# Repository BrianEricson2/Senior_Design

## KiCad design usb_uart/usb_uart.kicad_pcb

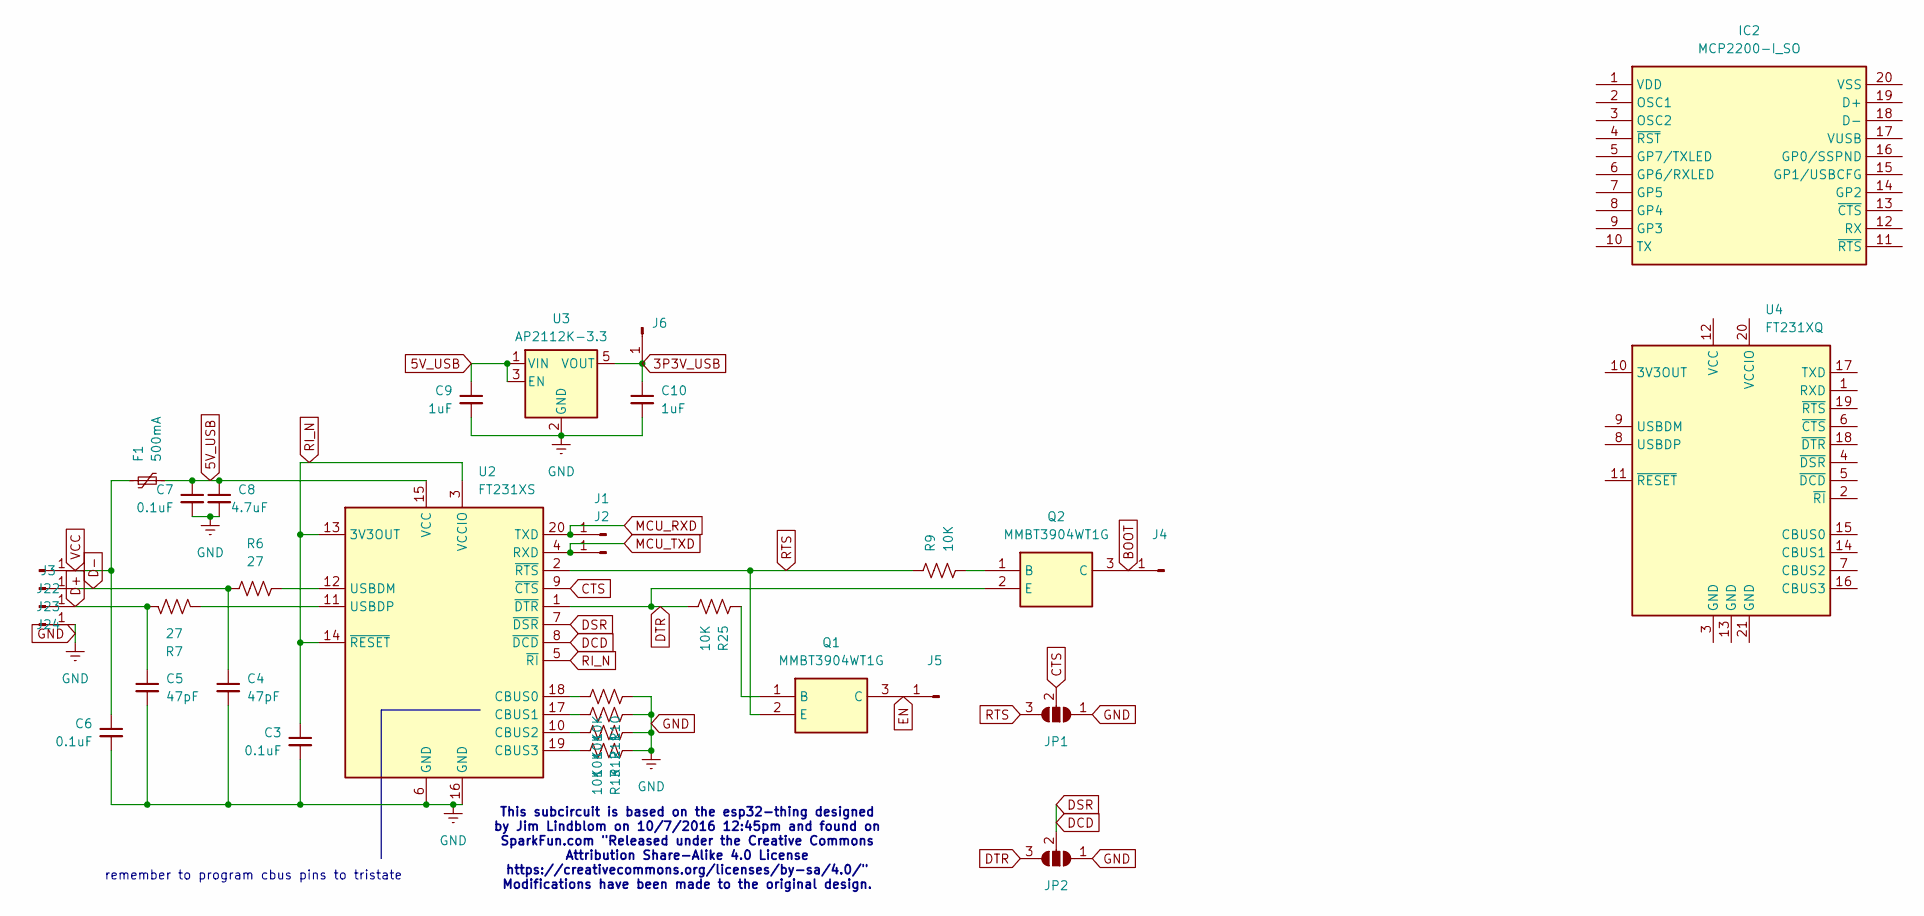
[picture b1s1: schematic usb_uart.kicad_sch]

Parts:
C3, C6, C7: 0.1uF; C_1206_3216Metric_Pad1.33x1.80mm_HandSolder
C4, C5: 47pF; C_1206_3216Metric_Pad1.33x1.80mm_HandSolder
C8: 4.7uF; C_1206_3216Metric_Pad1.33x1.80mm_HandSolder
C9, C10: 1uF; C_1206_3216Metric_Pad1.33x1.80mm_HandSolder
F1: 500mA; Fuse_1206_3216Metric_Pad1.42x1.75mm_HandSolder
IC2: MCP2200-I_SO; SOIC127P1030X265-20N; Mouser Part Number 579-MCP2200-I/SO
J1, J2, J3, J4, J5, J6, J22, J23, J24: Conn_01x01_Pin; PinHeader_1x01_P2.00mm_Vertical
JP1, JP2: SolderJumper_3_Open; SolderJumper-3_P1.3mm_Open_RoundedPad1.0x1.5mm_NumberLabels
Q1, Q2: MMBT3904WT1G; SOT65P220X100-3N; Mouser Part Number 863-MMBT3904WT1G
R6, R7: 27; R_1206_3216Metric_Pad1.30x1.75mm_HandSolder
R9, R10, R11, R12, R13, R25: 10K; R_1206_3216Metric_Pad1.30x1.75mm_HandSolder
U2: FT231XS; SSOP-20_3.9x8.7mm_P0.635mm
U3: AP2112K-3.3; SOT-23-5
U4: FT231XQ; QFN-20-1EP_4x4mm_P0.5mm_EP2.5x2.5mm

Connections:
3P3V_USB: C10.1, J6.1, U3.5 (VOUT)
5V_USB: C7.1, C8.1, C9.1, F1.2, U2.15 (VCC), U3.1 (VIN), U3.3 (EN)
BOOT: J4.1, Q2.3 (C)
CTS: JP1.2 (C), U2.9 (~CTS)
D+: C5.1, J23.1, R7.2
D-: C4.1, J22.1, R6.2
DCD: JP2.2 (C), U2.7 (~DSR), U2.8 (~DCD)
DTR: JP2.3 (B), Q2.2 (E), R25.2, U2.1 (~DTR)
EN: J5.1, Q1.3 (C)
GND: C3.2, C4.2, C5.2, C6.2, C7.2, C8.2, C9.2, C10.2, J24.1, JP1.1 (A), JP2.1 (A), R10.1, R11.1, R12.1, R13.1, U2.6 (GND), U2.16 (GND), U3.2 (GND)
MCU_RXD: J1.1, U2.20 (TXD)
MCU_TXD: J2.1, U2.4 (RXD)
unnamed: Q1.1 (B), R25.1
unnamed: Q2.1 (B), R9.2
unnamed: R10.2, U2.18 (CBUS0)
unnamed: R11.2, U2.17 (CBUS1)
unnamed: R12.2, U2.10 (CBUS2)
unnamed: R13.2, U2.19 (CBUS3)
unnamed: R6.1, U2.12 (USBDM)
unnamed: R7.1, U2.11 (USBDP)
RI_N: C3.1, U2.3 (VCCIO), U2.5 (~RI), U2.13 (3V3OUT), U2.14 (~RESET)
RTS: JP1.3 (B), Q1.2 (E), R9.1, U2.2 (~RTS)
VCC: C6.1, F1.1, J3.1

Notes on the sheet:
This subcircuit is based on the esp32-thing designed by Jim Lindblom on 10/7/2016 12:45pm and found on SparkFun.com "Released under the Creative Commons Attribution Share-Alike 4.0 License https://creativecommons.org/licenses/by-sa/4.0/" Modifications have been made to the original design.
remember to program cbus pins to tristate

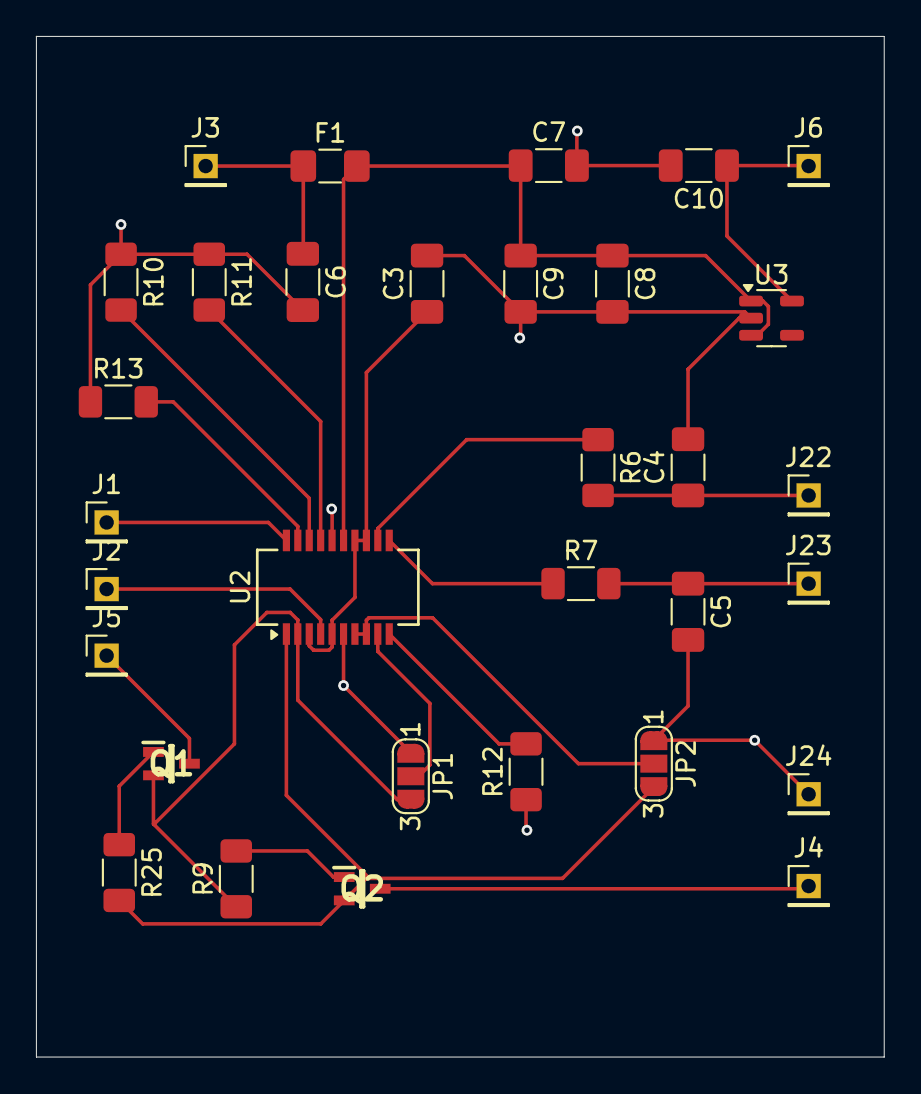
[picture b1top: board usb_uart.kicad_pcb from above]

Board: 2 copper layers, 47.1 x 56.7 mm, 32 parts (0 on the bottom side), 23 nets.

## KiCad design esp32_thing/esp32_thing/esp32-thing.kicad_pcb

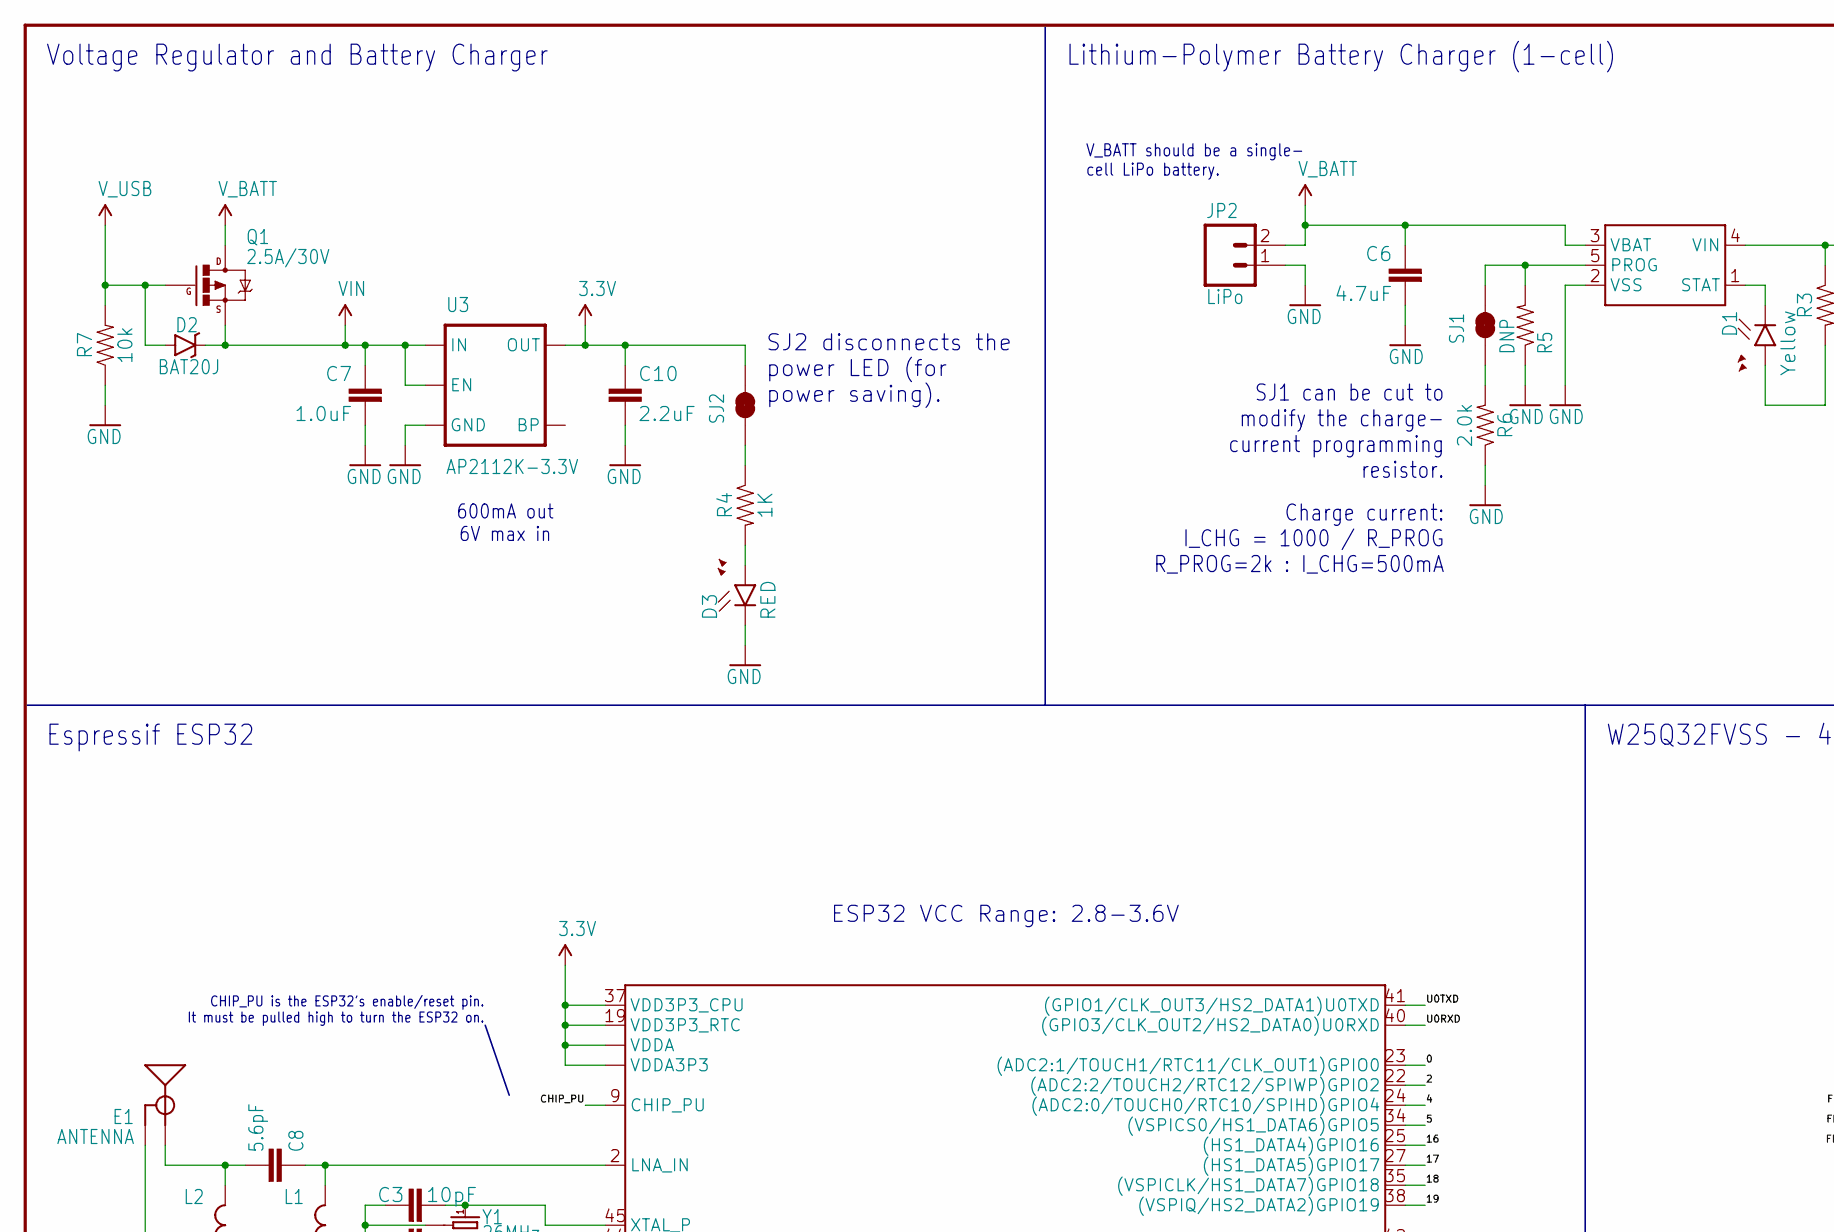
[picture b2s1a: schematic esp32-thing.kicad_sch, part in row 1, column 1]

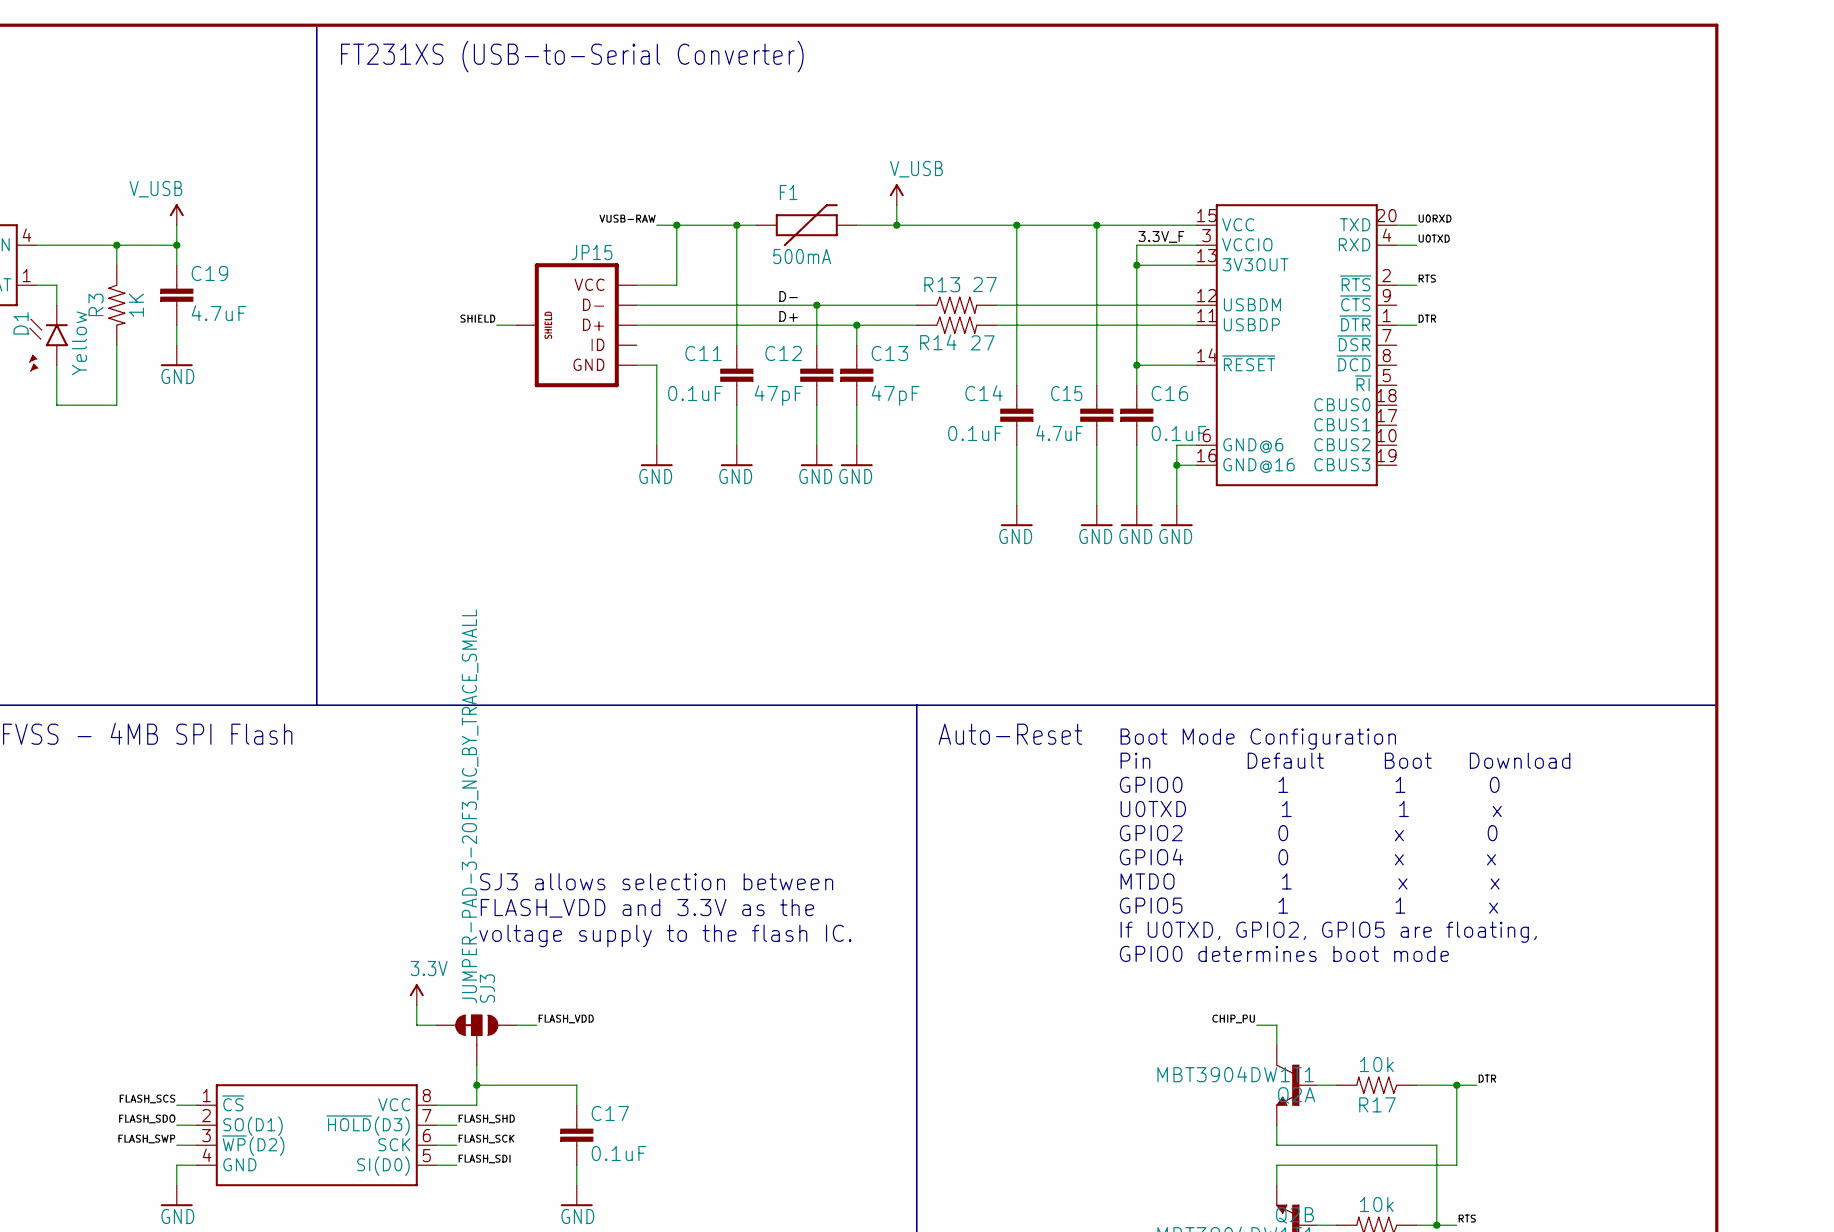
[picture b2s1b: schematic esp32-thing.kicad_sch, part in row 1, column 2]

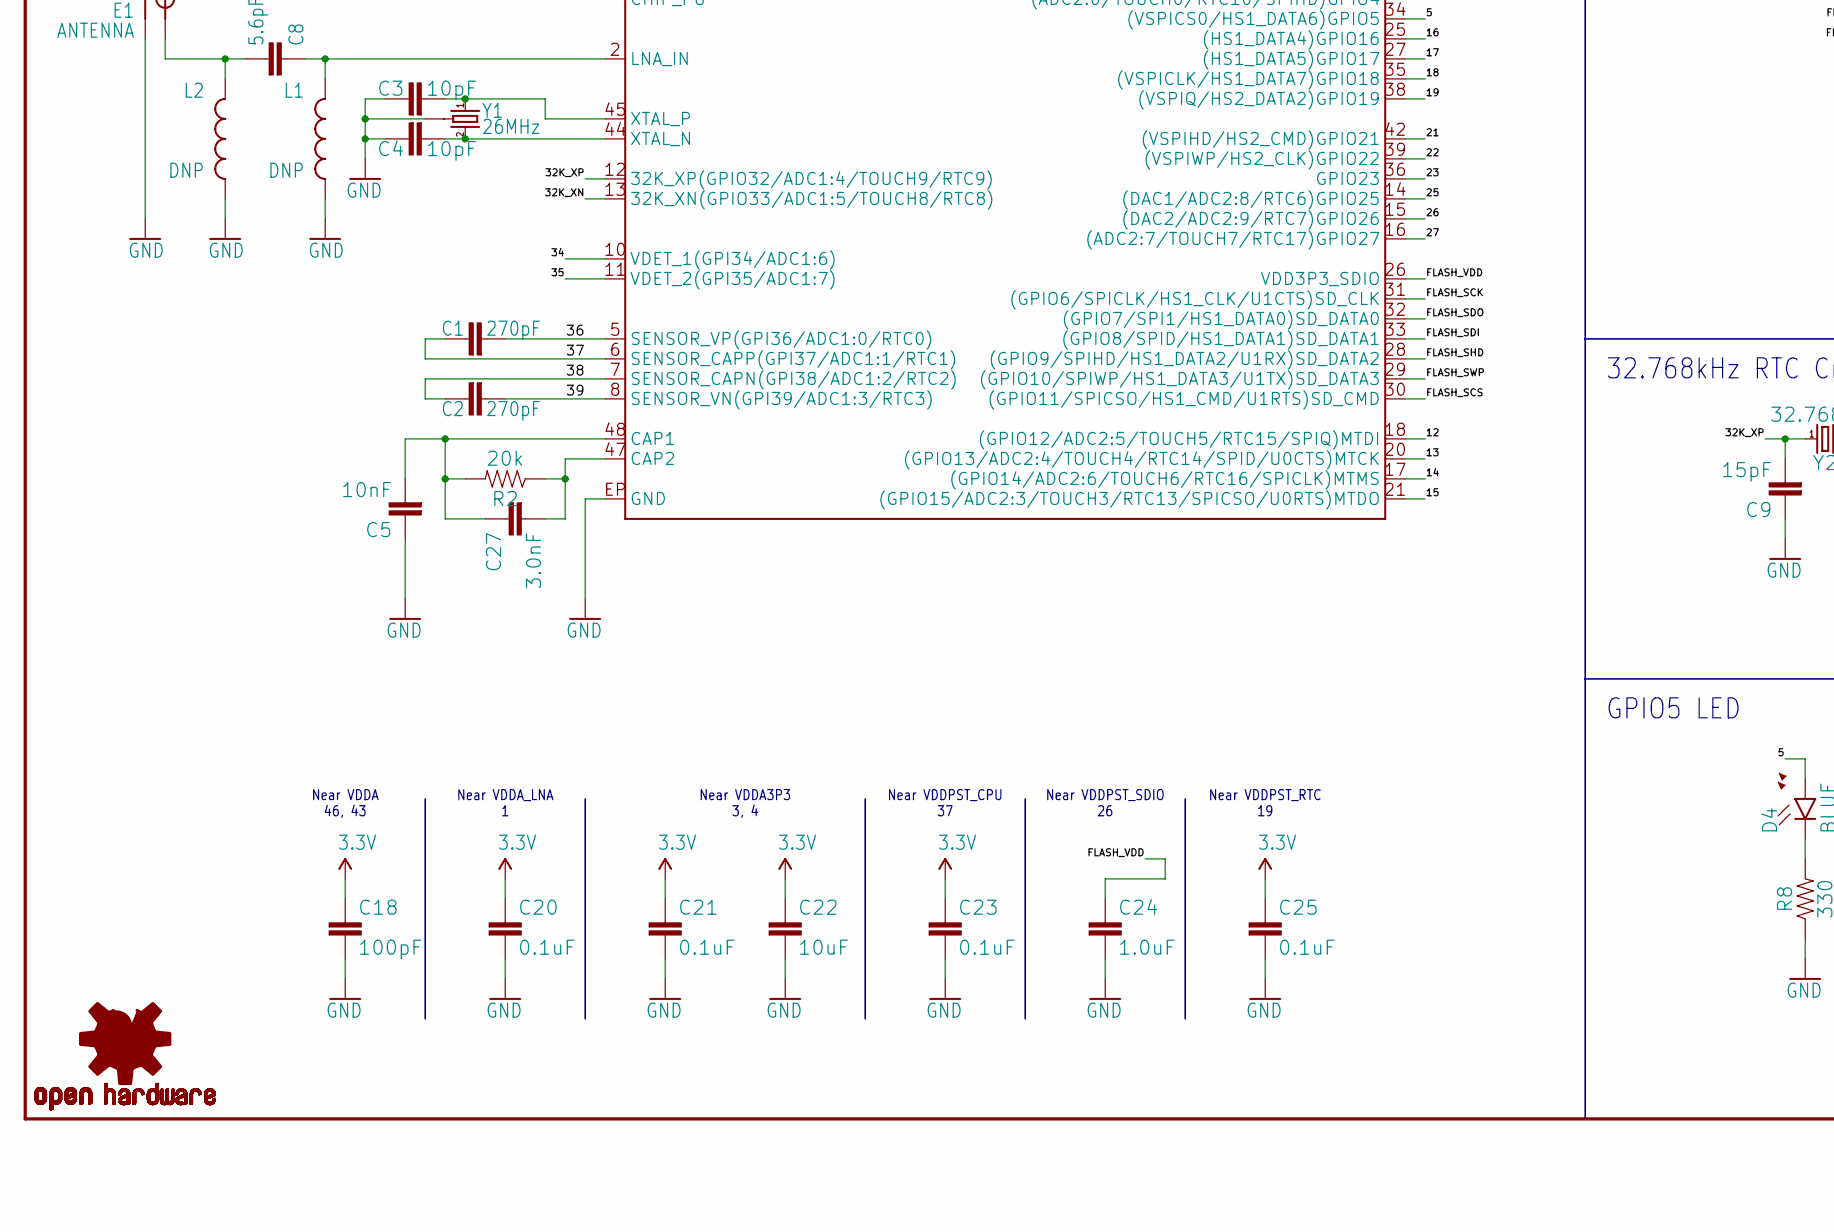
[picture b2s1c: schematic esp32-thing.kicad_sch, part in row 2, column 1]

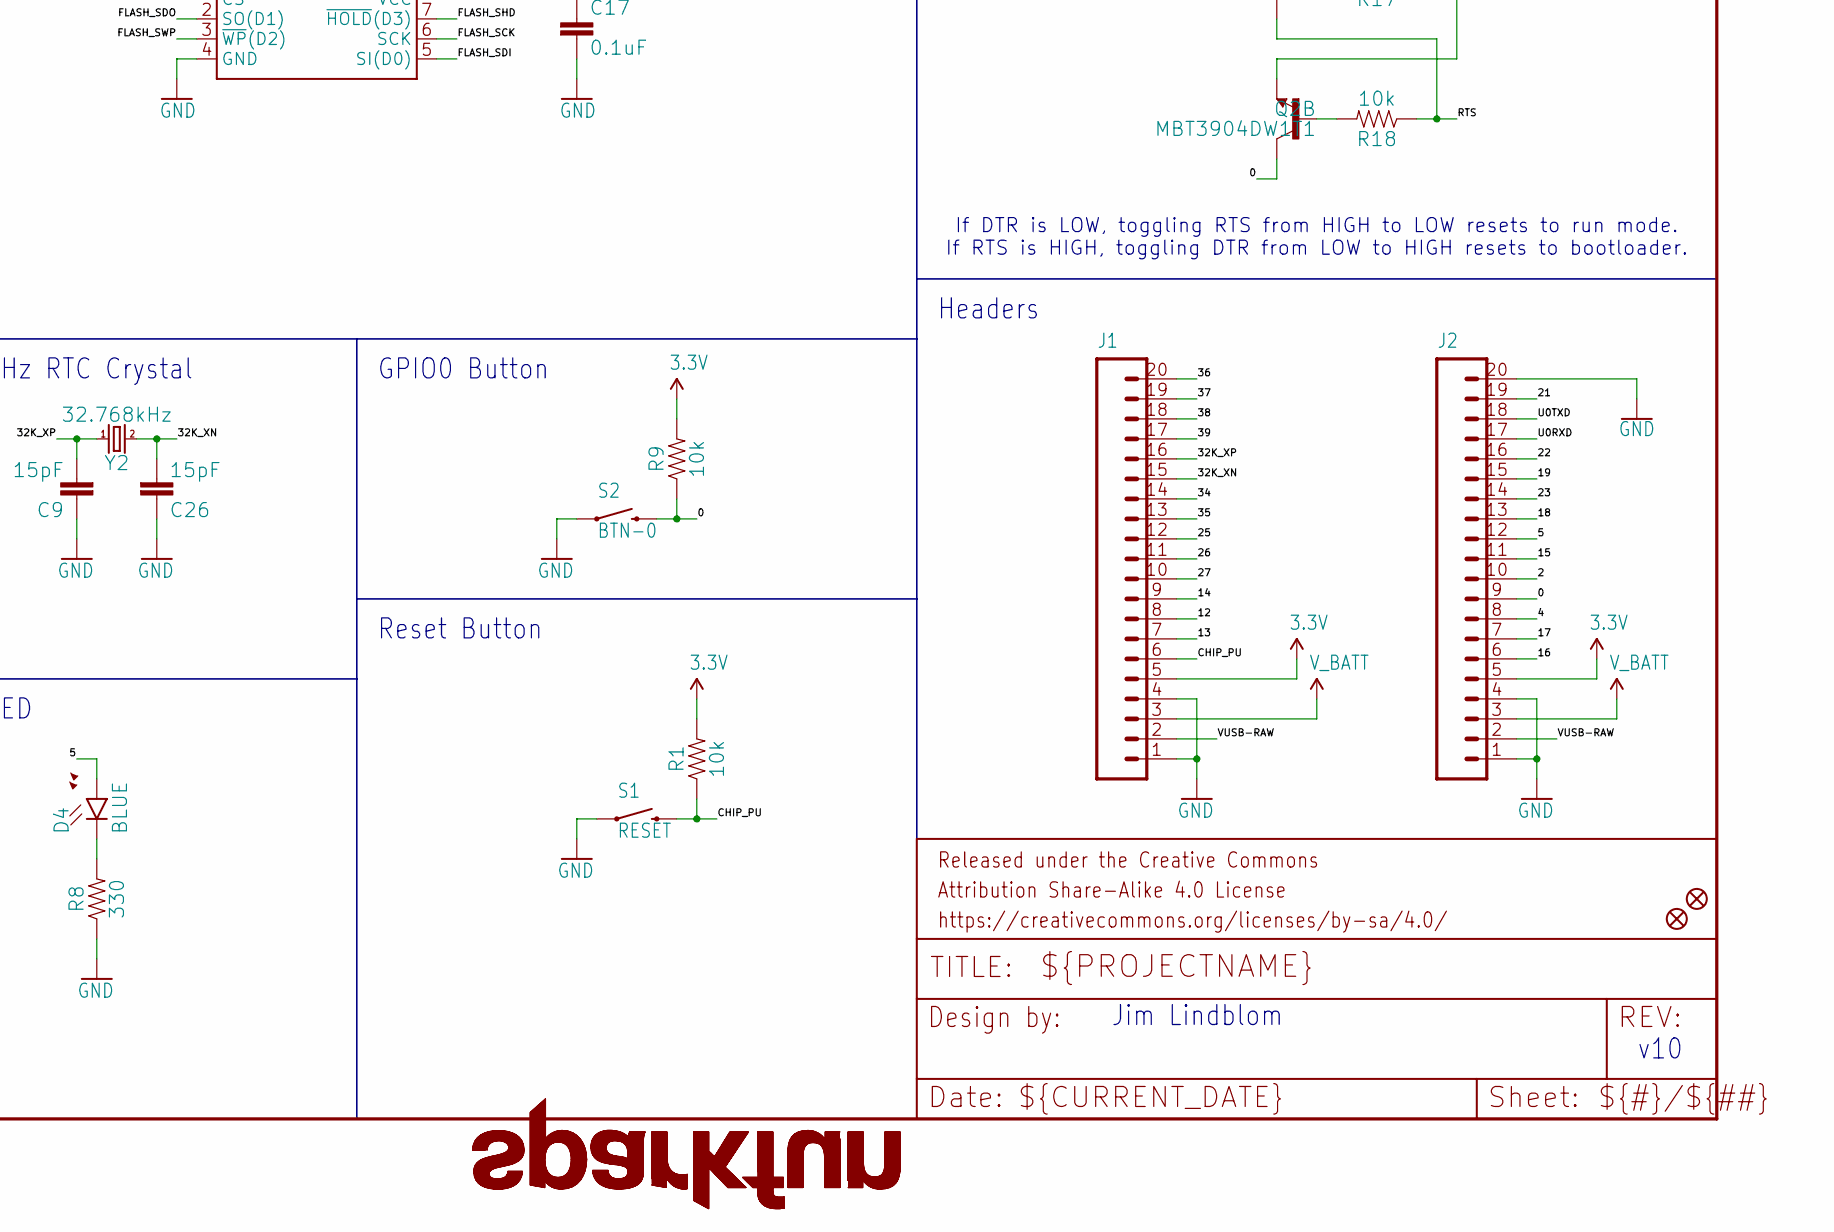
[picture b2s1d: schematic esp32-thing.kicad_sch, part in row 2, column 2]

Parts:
C1, C2: 270pF; 0603
C3, C4: 10pF; 0603
C5: 10nF; 0603
C6, C19: 4.7uF; 0603
C7: 1.0uF; 0805
C8: 5.6pF; 0603
C9, C26: 15pF; 0603
C10: 2.2uF; 0603
C11, C14, C16, C17, C20, C21, C23, C25: 0.1uF; 0603
C12, C13: 47pF; 0603
C15: 4.7uF; 0603-CAP
C18: 100pF; 0603
C22: 10uF; 0603
C24: 1.0uF; 0603
C27: 3.0nF; 0603
D1: Yellow; LED-0603
D2: BAT20J; SOD-323
D3: RED; LED-0603
D4: BLUE; LED-0603
E1: ANTENNA; TRACE_ANTENNA_2.4GHZ_25.7MM_TUNED
F1: 500mA; PTC-1206
FD1, FD2: FIDUCIALUFIDUCIAL; MICRO-FIDUCIAL
FRAME1: FRAME-LEDGER; CREATIVE_COMMONS
J1, J2: M20NOSILK; 1X20_NOSILK
JP2: LiPo; JST-2-PTH
JP15: USB_MICROB_PLUGCONN-11752; USB-B-MICRO-SMD_V03
L1, L2: DNP; 0603
LOGO1, LOGO3: SFE_LOGO_NAME.2_INCH; SFE_LOGO_NAME_.2
LOGO2: OSHW-LOGOMINI; OSHW-LOGO-MINI
Q1: 2.5A/30V; SOT23-3
Q2: MBT3904DW1T1; SC70-6
R1, R7, R9, R17, R18: 10k; 0603
R2: 20k; 0603
R3, R4: 1K; 0603
R5: DNP; 1_6W-RES
R6: 2.0k; 0603
R8: 330; 0603
R13, R14: 27; 0603
S1: RESET; TACTILE_SWITCH_SMD_4.6X2.8MM
S2: BTN-0; TACTILE_SWITCH_SMD_4.6X2.8MM
SJ1, SJ2: JUMPER-PAD-2-NC_BY_TRACE; PAD-JUMPER-2-NC_BY_TRACE_YES_SILK
SJ3: JUMPER-PAD-3-2OF3_NC_BY_TRACE_SMALL; PAD-JUMPER-3-2OF3_NC_BY_TRACE_YES_SILK_FULL_BOX
U1: MCP73831; SOT23-5
U2: ESP3212; QFN48-0.4MM
U3: AP2112K-3.3V; SOT23-5
U4: FT231XS; SSOP20_L
U5: W25Q32FVSS; SOIC-8
Y1: 26MHz; CRYSTAL-SMD-3.2X2.5
Y2: 32.768kHz; CRYSTAL-SMD-3.2X1.5MM

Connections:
0: J2.9, Q2.6 (C), R9.1, S2.3 (2), S2.4 (2), U2.23 ((ADC2:1/TOUCH1/RTC11/CLK_OUT1)GPIO0)
2: J2.10, U2.22 ((ADC2:2/TOUCH2/RTC12/SPIWP)GPIO2)
3.3V: C10.1, C18.1, C20.1, C21.1, C22.1, C23.1, C25.1, J1.5, J2.5, R1.2, R9.2, SJ2.2, SJ3.3, U2.1 (VDDA), U2.3 (VDDA3P3), U2.4 (VDDA3P3), U2.19 (VDD3P3_RTC), U2.37 (VDD3P3_CPU), U2.43 (VDDA), U2.46 (VDDA), U3.5 (OUT)
3.3V_F: C16.1, U4.3 (VCCIO), U4.13 (3V3OUT), U4.14 (~RESET)
4: J2.8, U2.24 ((ADC2:0/TOUCH0/RTC10/SPIHD)GPIO4)
5: D4.A, J2.12, U2.34 ((VSPICS0/HS1_DATA6)GPIO5)
12: J1.8, U2.18 ((GPIO12/ADC2:5/TOUCH5/RTC15/SPIQ)MTDI)
13: J1.7, U2.20 ((GPIO13/ADC2:4/TOUCH4/RTC14/SPID/U0CTS)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)
14: J1.9, U2.17 ((GPIO14/ADC2:6/TOUCH6/RTC16/SPICLK)MTMS)
15: J2.11, U2.21 ((GPIO15/ADC2:3/TOUCH3/RTC13/SPICSO/U0RT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)
16: J2.6, U2.25 ((HS1_DATA4)GPIO16)
17: J2.7, U2.27 ((HS1_DATA5)GPIO17)
18: J2.13, U2.35 ((VSPICLK/HS1_DATA7)GPIO18)
19: J2.15, U2.38 ((VSPIQ/HS2_DATA2)GPIO19)
21: J2.19, U2.42 ((VSPIHD/HS2_CMD)GPIO21)
22: J2.16, U2.39 ((VSPIWP/HS2_CLK)GPIO22)
23: J2.14, U2.36 (GPIO23)
25: J1.12, U2.14 ((DAC1/ADC2:8/RTC6)GPIO25)
26: J1.11, U2.15 ((DAC2/ADC2:9/RTC7)GPIO26)
27: J1.10, U2.16 ((ADC2:7/TOUCH7/RTC17)GPIO27)
32K_XN: C26.2, J1.15, U2.13 (32K_XN(GPIO33/ADC1:5/TOUCH8/RTC8)), Y2.P$2 (2)
32K_XP: C9.2, J1.16, U2.12 (32K_XP(GPIO32/ADC1:4/TOUCH9/RTC9)), Y2.P$1 (1)
34: J1.14, U2.10 (VDET_1(GPI34/ADC1:6))
35: J1.13, U2.11 (VDET_2(GPI35/ADC1:7))
36: C1.2, J1.20, U2.5 (SENSOR_VP(GPI36/ADC1:0/RTC0))
37: C1.1, J1.19, U2.6 (SENSOR_CAPP(GPI37/ADC1:1/RTC1))
38: C2.1, J1.18, U2.7 (SENSOR_CAPN(GPI38/ADC1:2/RTC2))
39: C2.2, J1.17, U2.8 (SENSOR_VN(GPI39/ADC1:3/RTC3))
CAP_10N: C5.2, C27.1, R2.2, U2.48 (CAP1)
CHIP_PU: J1.6, Q2.3 (C), R1.1, S1.3 (2), S1.4 (2), U2.9 (CHIP_PU)
D+: C13.1, JP15.D+, R14.1
D-: C12.1, JP15.D-, R13.1
DTR: Q2.1 (E), R17.1, U4.1 (~DTR)
FLASH_SCK: U2.31 ((GPIO6/SPICLK/HS1_CLK/U1CTS)SD_CLK), U5.6 (SCK)
FLASH_SCS: U2.30 ((GPIO11/SPICSO/HS1_CMD/U1RTS)SD_CMD), U5.1 (~CS)
FLASH_SDI: U2.33 ((GPIO8/SPID/HS1_DATA1)SD_DATA1), U5.5 (SI(D0))
FLASH_SDO: U2.32 ((GPIO7/SPI1/HS1_DATA0)SD_DATA0), U5.2 (SO(D1))
FLASH_SHD: U2.28 ((GPIO9/SPIHD/HS1_DATA2/U1RX)SD_DATA2), U5.7 (~HOLD(D3))
FLASH_SWP: U2.29 ((GPIO10/SPIWP/HS1_DATA3/U1TX)SD_DATA3), U5.3 (~WP(D2))
FLASH_VDD: C24.1, SJ3.1, U2.26 (VDD3P3_SDIO)
GND: C3.1, C4.1, C5.1, C6.2, C7.2, C9.1, C10.2, C11.2, C12.2, C13.2, C14.2, C15.2, C16.2, C17.2, C18.2, C19.2, C20.2, C21.2, C22.2, C23.2, C24.2, C25.2, C26.1, D3.C, E1.GND, E1.GND2 (GND), J1.1, J1.4, J2.1, J2.4, J2.20, JP2.1, JP15.GND, L1.2, L2.2, R5.1, R6.1, R7.1, R8.1, S1.1, S1.2 (1), S2.1, S2.2 (1), U1.2 (VSS), U2.EP (GND), U3.2 (GND), U4.6 (GND@6), U4.16 (GND@16), U5.4 (GND), Y1.2 (GND), Y1.4 (GND)
LNA_IN: C8.1, L1.1, U2.2 (LNA_IN)
unnamed: D4.C, R8.2
unnamed: D3.A, R4.2
unnamed: R4.1, SJ2.1
unnamed: C27.2, R2.1, U2.47 (CAP2)
unnamed: R13.2, U4.12 (USBDM)
unnamed: R14.2, U4.11 (USBDP)
unnamed: D1.C, U1.1 (STAT)
unnamed: Q2.5 (B), R17.2
unnamed: C17.1, SJ3.2, U5.8 (VCC)
unnamed: Q2.2 (B), R18.2
unnamed: C3.2, U2.45 (XTAL_P), Y1.1
unnamed: R5.2, SJ1.2, U1.5 (PROG)
unnamed: C4.2, U2.44 (XTAL_N), Y1.3 (2)
unnamed: R6.2, SJ1.1
unnamed: D1.A, R3.2
RTS: Q2.4 (E), R18.1, U4.2 (~RTS)
SHIELD: JP15.SHIELD1 (SHIELD), JP15.SHIELD2 (SHIELD), JP15.SHIELD3 (SHIELD)
TRACE_ANT: C8.2, E1.ANT (SIGNAL), L2.1
U0RXD: J2.17, U2.40 ((GPIO3/CLK_OUT2/HS2_DATA0)U0RXD), U4.20 (TXD)
U0TXD: J2.18, U2.41 ((GPIO1/CLK_OUT3/HS2_DATA1)U0TXD), U4.4 (RXD)
VIN: C7.1, D2.C, Q1.2 (S), U3.1 (IN), U3.3 (EN)
VUSB-RAW: C11.1, F1.1, J1.2, J2.2, JP15.VBUS (VCC)
V_BATT: C6.1, J1.3, J2.3, JP2.2, Q1.3 (D), U1.3 (VBAT)
V_USB: C14.1, C15.1, C19.1, D2.A, F1.2, Q1.1 (G), R3.1, R7.2, U1.4 (VIN), U4.15 (VCC)

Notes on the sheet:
Headers
If DTR is LOW, toggling RTS from HIGH to LOW resets to run mode. If RTS is HIGH, toggling DTR from LOW to HIGH resets to bootloader.
Espressif ESP32
V_BATT should be a single- cell LiPo battery.
SJ2 disconnects the power LED (for power saving).
32.768kHz RTC Crystal
SJ1 can be cut to modify the charge- current programming resistor.
Near VDDA3P3 3, 4
GPIO0 Button
Jim Lindblom
Near VDDPST_SDIO 26
Boot Mode Configuration Pin Default Boot Download GPIO0 1 1 0 U0TXD 1 1 x GPIO2 0 x 0 GPIO4 0 x x MTDO 1 x x GPIO5 1 1 x If U0TXD, GPIO2, GPIO5 are floating, GPIO0 determines boot mode
Lithium-Polymer Battery Charger (1-cell)
W25Q32FVSS - 4MB SPI Flash
600mA out 6V max in
ESP32 VCC Range: 2.8-3.6V
Near VDDA 46, 43
GPIO5 LED
Auto-Reset
CHIP_PU is the ESP32's enable/reset pin. It must be pulled high to turn the ESP32 on.
Charge current: I_CHG = 1000 / R_PROG R_PROG=2k : I_CHG=500mA
Voltage Regulator and Battery Charger
Near VDDPST_CPU 37
Reset Button
FT231XS (USB-to-Serial Converter)
Near VDDA_LNA 1
SJ3 allows selection between FLASH_VDD and 3.3V as the voltage supply to the flash IC.
Near VDDPST_RTC 19
v10

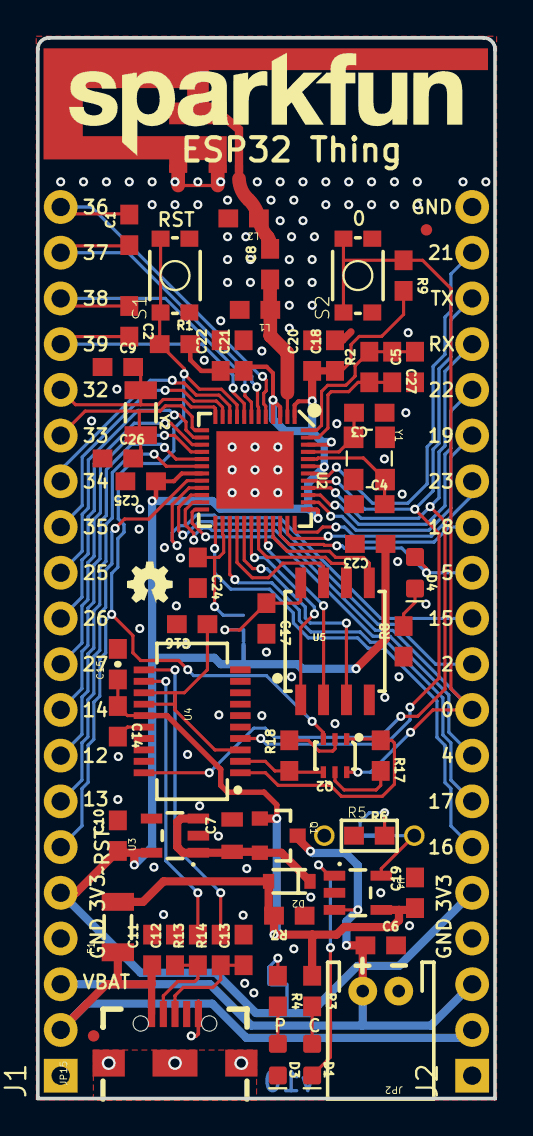
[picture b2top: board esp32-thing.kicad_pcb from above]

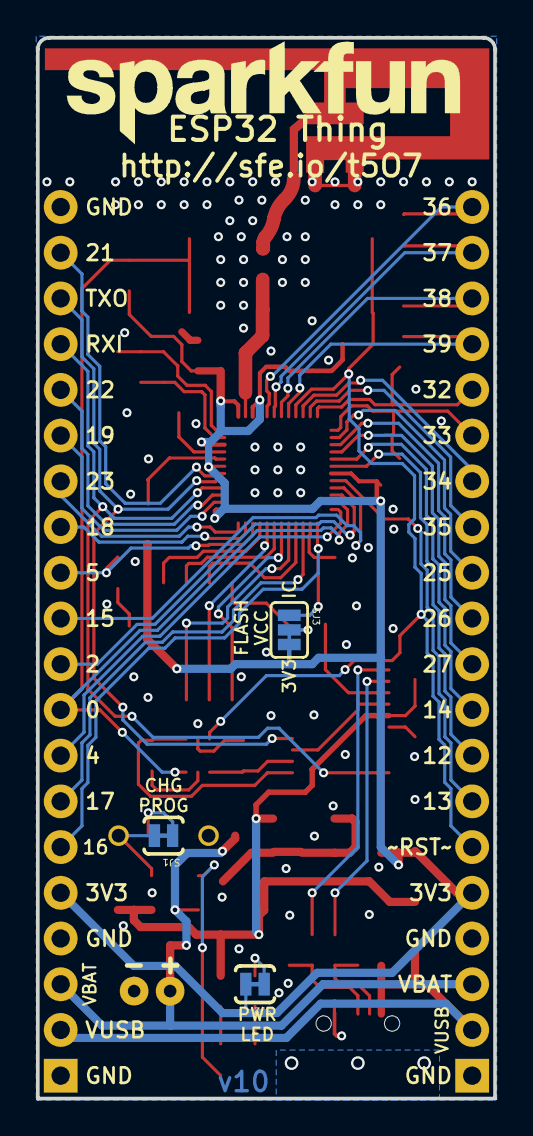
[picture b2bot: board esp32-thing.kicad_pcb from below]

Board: 2 copper layers, 25.4 x 58.9 mm, 72 parts (4 on the bottom side), 66 nets.

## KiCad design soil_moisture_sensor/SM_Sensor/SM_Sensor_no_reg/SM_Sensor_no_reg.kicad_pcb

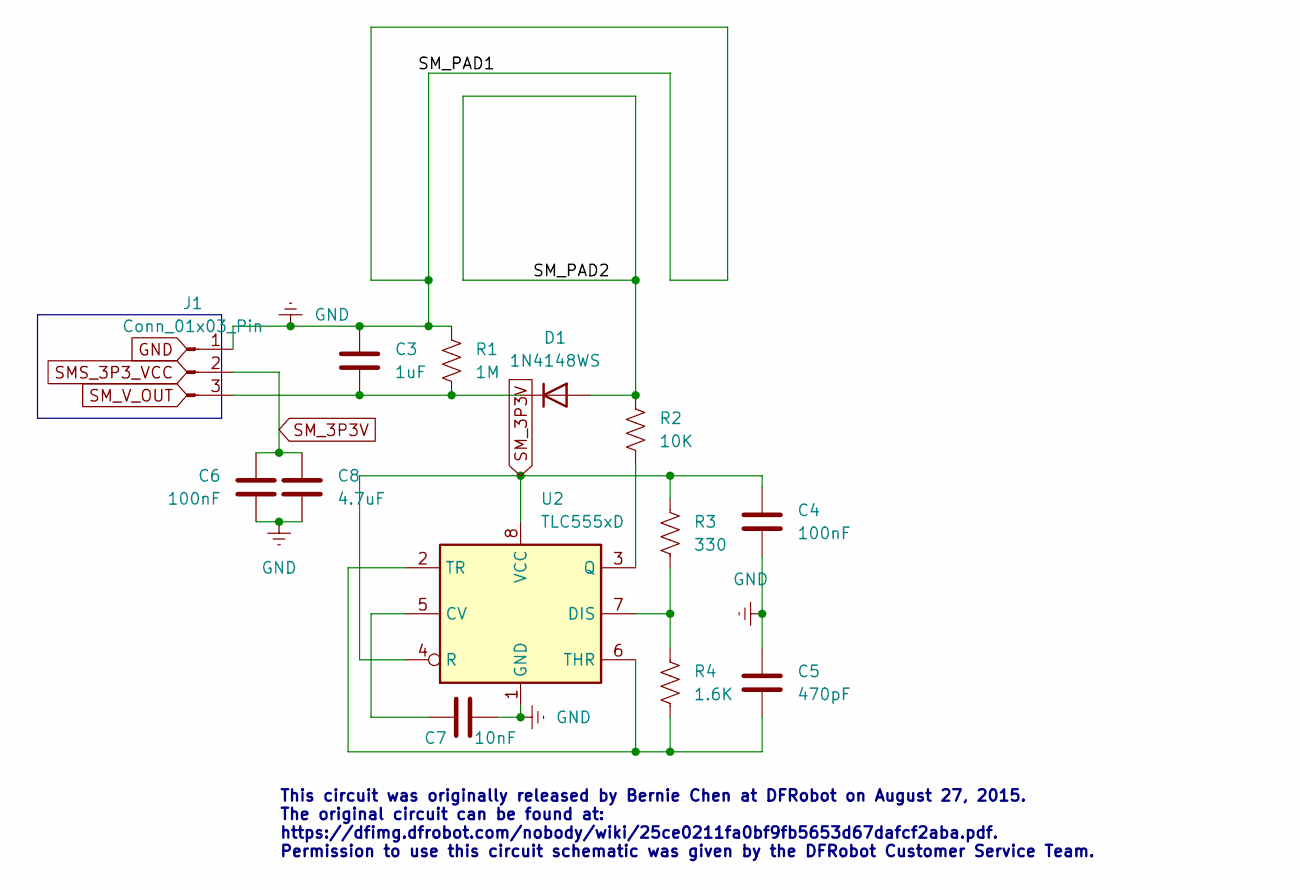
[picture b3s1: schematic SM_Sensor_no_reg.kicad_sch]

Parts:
C3: 1uF; C_1210_3225Metric_Pad1.33x2.70mm_HandSolder
C4, C6: 100nF; C_1210_3225Metric_Pad1.33x2.70mm_HandSolder
C5: 470pF; C_1210_3225Metric_Pad1.33x2.70mm_HandSolder
C7: 10nF; C_1210_3225Metric_Pad1.33x2.70mm_HandSolder
C8: 4.7uF; C_1210_3225Metric_Pad1.33x2.70mm_HandSolder
D1: 1N4148WS; D_SOD-323
J1: Conn_01x03_Pin; PinHeader_1x03_P1.27mm_Vertical
R1: 1M; R_1210_3225Metric_Pad1.30x2.65mm_HandSolder
R2: 10K; R_1210_3225Metric_Pad1.30x2.65mm_HandSolder
R3: 330; R_1210_3225Metric_Pad1.30x2.65mm_HandSolder
R4: 1.6K; R_1210_3225Metric_Pad1.30x2.65mm_HandSolder
U2: TLC555xD; SOIC-8_3.9x4.9mm_P1.27mm

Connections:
/SM_PAD2: D1.2 (A), R2.1
GND: C3.1, C4.2, C5.2, C6.2, C7.1, C8.2, J1.1, R1.1, U2.1 (GND)
unnamed: C3.2, D1.1 (K), J1.3, R1.2
unnamed: C7.2, U2.5 (CV)
unnamed: R3.2, R4.1, U2.7 (DIS)
unnamed: R2.2, U2.3 (Q)
unnamed: C5.1, R4.2, U2.2 (TR), U2.6 (THR)
SM_3P3V: C4.1, C6.1, C8.1, J1.2, R3.1, U2.4 (R), U2.8 (VCC)

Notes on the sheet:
This circuit was originally released by Bernie Chen at DFRobot on August 27, 2015. The original circuit can be found at: https://dfimg.dfrobot.com/nobody/wiki/25ce0211fa0bf9fb5653d67dafcf2aba.pdf. Permission to use this circuit schematic was given by the DFRobot Customer Service Team.

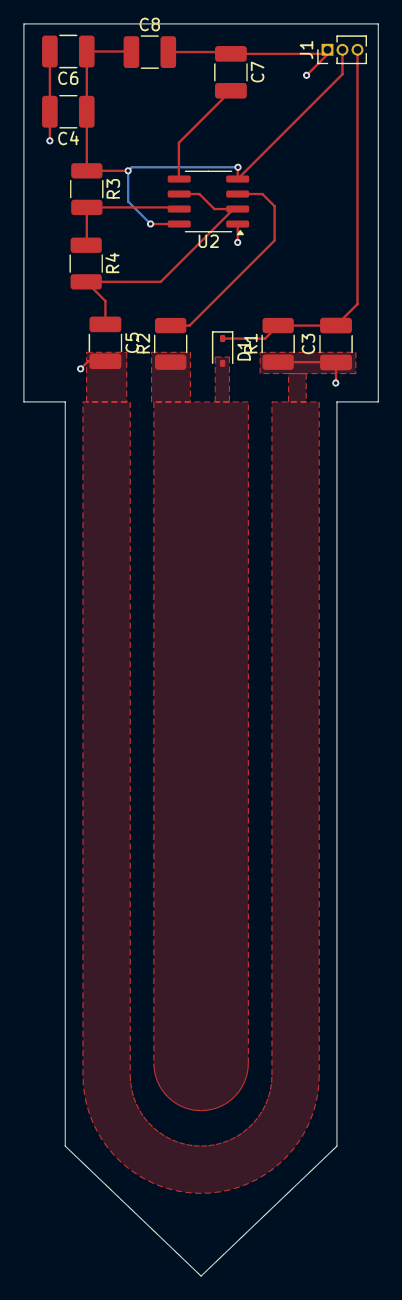
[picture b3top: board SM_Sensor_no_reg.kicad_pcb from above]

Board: 2 copper layers, 30.0 x 106.0 mm, 13 parts (0 on the bottom side), 8 nets.
